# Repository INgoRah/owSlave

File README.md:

# owSlave2
Fork from https://git.smho.de/gw/?p=owSlave2.git;a=summary, License

I2C master code from an unofficial github repository for Peter Fleury's I2C library
http://homepage.hispeed.ch/peterfleury/avr-software.html#libs now cloned to
https://github.com/alx741/avr_i2c.git
License GPL v3

## Changes
Version 1.9, 2025-12-18
- Decreased button press min times
- DS1820: no periodic measurement by the watchdog timer any more. The
  temperature is measured on the master's Convert T (and once after
  start), like a real DS18x20; the master polls, e.g. once a minute.
  The watchdog is a watchdog again for these builds as well
  (WDT_ENABLED), the ADC averaging takes its 4 samples at once.
- DS1820 (dual ROM): Skip ROM + Convert T (CC 44) starts the
  measurement of all sensors on the bus at once. Other commands after
  Skip ROM are ignored.
- Buttons: the release after a long press is reported with at least
  11 (352 ms) as press time. The device sleeps once the long press is
  signaled and millis() stands still, the master (> 350 ms) took the
  release for a short press. A short press never reports 0 (that is
  the long press started), the press time is capped at 0xfe.
- Bootloader on long lines, as the application does it: a 0 sent is
  pulled low within a few cycles of the master's fall (was 2..3 us,
  against the master's active pullup) and held 50 us (OWT_WRITE, was
  30 us). With several devices on a long line the bits sent got lost
  (the INFO answer garbled, "no bootloader answers" in in10dfs).
- Bootloader: works with the slots of the DS2482 on a loaded line. In
  a write 0 slot the DS2482 keeps the line low for 64 us and starts
  the next slot 5.25 us later; the bootloader waited for the line to
  be high for 2..3 us first (against ringing), with the rise time of a
  long line that was missed and the next slot with it - all bits
  shifted, no answer (INFO all ff) or a wrong CRC. The falling edge is
  now taken from the edge flag of INT0 (polled, no interrupt), as the
  application does by its interrupt: seen however short the high was.
  Against ringing a fall starts a slot only if the line is low again
  2..4 us later, falls up to 25 us after it are part of the same slot.
- Bootloader: a 0 sent is held 40 us (was 50): with the RC oscillator
  10 % slow the work between two bytes did not fit before the next
  slot. The CRC16 is updated a bit at a time in its slot.
- Bootloader: the result of a page write is sent from the start of a
  byte of the master (page 0 of the ATtinys takes 18 ms, the master is
  reading by then), the presence pulse of another device lasting
  longer than its own is not taken for the next reset.
- ATmega: INT0 is set to low level before power down (ISC01 is in EICRA,
  not MCUCR as on the ATtinys): with the falling edge the device did not
  wake up from power down by the bus.
- Fix a bug, when the watchdog fires after any left over 1-wire activity (which is
  still in spec).
  This is solved with that soft watchdog timer of 1 second.
  That could have caused issues on broken masters when a transfer
  is stopped after reset and could have also blocked pin detection
- Watchdog behaviour changed: first a soft watchdog fires after 1s and
  resets internal states, alarms and triggers a hard watchdog
  for 60 ms if the system does not go to normal.
- status field retuns 0x08 for soft watchdog, 0x88 for hard (as before)
- Fix CRC overwrite when the config command is used. That was causing a
  fallback to fixed owids (compile time)

Version 1.8, 2024-11-28
- Dual DS2450 (ADC) support and minor fixes
- the cfg read on the custom space seems not to be working yet
  on dual ROM
- Alarm on watchdog reset

Version 1.7, 2024-11-22
- Timer based switch (supports one timer only)
- Single Pin configuration message and new custom config space (first byte = 1)
- Read out custom space by first writing one config byte with 1 then reading
- Auto toggle now signals the latch and the output

Version 1.5, 2021-11-28
- Temperature and Humidity support with DHT22 on pin PB0 (compile option)
  Humiditiy is reported in the byte #5 instead of FF

Version 1.4, 2021-10-27
- support BMP280 with dual rom with DS1820 on a soft I2C master
- report any latch change even for auto switch
- remove latch output on configured input pins

Version 1.3, 2021-01-14
- Split the files for 2408 and 1820
- In case of temperature support, regularly wake up and check alarms thresholds.
  This is using watchdog timer - power optimized.
- Temperature controlled switch (heating control, thresholds configurable
- Temperature change reporting (configurable)
- Read initial state for input switches of types CFG_PASS* and perform auto switch.
    Otherwise a thermostat might be ignored on restart and no heating active where
    it should
- per port pin intialization to reduce power if not connected (pull up not needed)

Version 1.2
- For PWM output (on ATTiny85 PB4 / PIO0 and ATTiny84 PA5) the all output latch bits
  are used for the duty cycle (bightnes), 0 for off
- PWM output level to be applied on change request (not only on switching it on)
- optimize touch sensor handling (active high, no bouncing, just rising edge with validation).
    POL and SW_ID to be implemented

Version 1.1
- Interrupt generation using the ow line low for 900 us
- Timer functions like in Arduino but on polling base within the loop. No wakeup from sleep
- Pin and push button validation
- Watchdog support:
    After 8 secs of invalid state a reset occurs (e.g. a hang in button validation).
    This also applies to pressing a button for 8 secs (force reset)
- Initial OneWire ID is initialized and copyied over to the end of EEPROM on
  first boot for reading next time.
- store new config / custom command or newid command feature

## To Do
[x] Generate alarm for latch even when auto switching
[x] Support for timer switches using upper auto switching bits [4..7]: 1 - 30 secs, 2 - 1 min, 3 - 2 mins .. 15 - 14 min.
[ ] Watchdog fires if switching PIO without polling/resetting alarm
[ ] regression testing signal generation and improvements (bus detection and delay)
[ ] Disarm interrupt on reset pulse and arm again afterwards.
    Needs check wether slave can cope with just a reset without ROM commands.
    Timeout after reset?
[ ] iButton type 2 interrupt (assert reset for long time).
    Needs master improvements detecting it and slave ASM code extending the reset low time
[ ] Dual 2408 with on PCF8473
[ ] Pin overlay for in and out using all 10 pins (reset and 1-wire not available)

## Issues
[ ] long press no longer working with outstanding changes
[ ] config save does not work sometimes
[ ] once setting PIO overides heating override ... fixed by pin change corrections?
[ ] If bad signals on the bus or power outage OW ID could be damaged. Needs protection

  # Documentation

  ## Configuration

  ### EEPROM Layout
  See eeprom.py script

  ### Configuration Definition
  CFG [0] config control, see below; reads 0xff
  CFG [1] default 0xff unused
  CFG [2] default 0xff unused
  SWx  [3..10]
    Auto switch an ouput on (short) press of this pin. Output starts with 1 (1 switches PIO0...).
    Example: SW4 = 0x01 switches PI0 on latch 4
    0x80 disables it,
    0x20 timer based switching, look up in custom config space
    0x40 reserved for long press auto switching, look up in custom config space
  CFGx [11..18] see CFG_xxx defines
  FEA [19] - Feature if bit is cleared: 
    0x1 can do temperature
    0x2 can do ADC for brightness read
    0x4 supports pin timers and extended auto switching
  Reserved [20]
  Version [21..22]
  Type [23]

  ### Config control
  Byte 0 of a config write (0x86) tells what the write is (CC_xxx in
  DS2408.h):

  Byte 0 | Write | Done after
  -------- | -------- | --------
  0x00, 0xff, 0x10 .. 0xff not below | config_info, saved with Version = 0x55 | 23 bytes
  0x01 | custom config (cfg_custom1, TIMER_SUPPORT), saved with byte 22 = 0x55 | 23 bytes
  0x02 | config_info2 (dual ROM), by its own write command for now | 23 bytes
  0x03 .. 0x0f | reserved, ignored | -
  0xB0 | bootloader: `B0 07 F8` (BL_ENTER_KEY and its complement) | 3 bytes
  0xDE | test: `DE AD op`, op 0x01 soft reset, 0x02 soft then hard reset, 0xff hard reset | 3 bytes

  The commands (0xB0, 0xDE) do not touch config_info, the bytes after
  the third are ignored. A config read starts with 0xff, written back
  as it is it is a plain config write.

## 1-Wire bootloader (ATmega88, ATmega168, ATtiny84, ATtiny85)

`bootloader/` is a bootloader for a firmware update over the 1-Wire bus
(in10dfs: write the image to `<rom>/firmware`), protocol in
`include/owbootloader.h`. It answers with the device's own ROM (from
the EEPROM). After a reset it starts the application at once, unless
the application asked for the update (config write `0xB0 0x07 0xF8`,
see "Config control", it jumps to the bootloader with BL_MAGIC in r24:r25) or there is
no valid application. Without anything to do for a minute it starts
the application again. An update broken off leaves no application:
the device stays in its bootloader, the update can be done again.

| | bootloader | application | fuses |
|---|---|---|---|
| ATmega88 | boot section, 2 KB at 0x1800 | 6144 bytes | efuse 0xF8: BOOTSZ 1024 words, BOOTRST |
| ATmega168 | boot section, 2 KB at 0x3800 | 14336 bytes | efuse 0xF8: BOOTSZ 1024 words, BOOTRST |
| ATtiny84/85 | 1600 bytes at 0x19C0 | 6592 bytes | efuse 0xFE: SELFPRGEN |

The ATtinys have no boot section: reset always starts at 0. Writing
page 0 the bootloader puts its own reset vector there and keeps the
application's on the last page of the flash, to start it by; a read
of page 0 gives the page as written. On the ATtiny85, without a 16 bit
timer, Timer0 is extended to 16 bit in software.

The environments: `atmega88`, `atmega168`, `attiny84-bl`, `attiny85-bl` for the
application (`-DBL_SUPPORT`), `<mcu>-boot` for the bootloader. By ISP,
once, the fuses and both together - an ISP upload erases the chip, the
upload of `<mcu>-boot` writes the application as well:

```sh
pio run -e attiny84-bl && pio run -e attiny84-boot -t fuses -t upload
```

`-t fuses` erases the chip, so only with the upload. Afterwards the
application is updated over the bus.

`test/bootloader/run.sh [mcu ...]` runs bootloader and application in
simavr against a 1-Wire master with the timing of a DS2482: into the
bootloader (on the ATtinys made by the test, simavr does not run the
application's 1-Wire there), INFO, Read and Search ROM, page writes, an
update as in10dfs does it, a reset in the middle of it, back to the new
application and in once more. It needs the simavr headers (libsimavr-dev,
or SIMAVR_INC).

## Custom timer command

0xC5 | FEAT/PIN | TYPE | VAL1 | VAL2
read back 16 bit CRC over command and all bytes
TYPE: see TMR_TYPE_xxx definitions
VAL1: Time in 10ms or config for non static switch. If 0 use the confiugred default time.
      In case of type E3 (TMR_TYPE_BRIGHTNESS) or E5 (TMR_TYPE_THRESHOLD) 
      brightness or lower threshold value for darkness switching.
      Brightness is the inversed ligth - means 0xff dark and 0 for very bright.
      code: switch only if brightness >= cfg_custom1[1]
      Configuring threshold will also store the entire custom cfg in EEPROM
VAL2: Level 0 .. 255 for PWM output

Status represents a running timer with 0x20 or a dimming down with 0x40

# 1-wire implementation (from tm3e.de / German)

## Files

Datei  | Beschreibung |
-------- | -------- |
OWPinInterrupt.s | Interrupt für Pegeländerungen am 1-Wire Pin
OWTimerInterrupt.s | Timer Interrupt für Zeitmessungen
OWConfig.s | Allgemeine Konfiguration (Register und Speicher Belegung, Auswahl der Konfiguration für den speziellen AVR, Macros)
OWSet_ATTINYX4.s | Spezielle Konfiguration für ATTINY24 - ATTINY84
OWSet_ATTINYX5.s | Spezielle Konfiguration für ATTINY25 - ATTINY85
OWCRC8.s | CRC8 Berechnung (Wird je nach Gerät ausgewählt)
OWCRC16.s | CRC16 Berechnung (Wird je nach Gerät ausgewählt)
OWRomFunctions.s | Alle ROM-Funktionen, sowie die Funktionalität zur Änderung der OW-Pin
Diese Dateien stehen im Unterverzeichnis "common". Für jedes 1-Wire Gerät wird ein weiteres Unterverzeichnis angelegt und dort ist mindestens jeweils eine .c Datei mit dem Hauptprogramm und eine .s Datei mit den spezifischen Assemblerroutinen für das Gerät.

## Register und Variablen
Alle Registerbezeichnungen beginnen mit "r_", so dass sie nicht mit Variablen verwechselt werden können. Wenn es dazugehörige Variablen im SRAM gibt, dann stehen sie gleich dahinter.

 Bezeichnung | Nr. | Hauptfunktion |
 -------- | -------- | --- |
 r_temp | 16 | temporäre Zwischenspeicherung
 r_rwbyte / rwbyte | 17 | aktuelles Byte welches gelesen oder geschrieben wird
 r_temp2 | 18 | temporäres Zusatzregister, wenn eins nicht ausreicht
 r_bcount / bcount | 19 | Bit, welches gerade behandelt wird ist 1, Bit wird druchgeschoben. r_bcount=0 bedeutet: nächstes Byte muss behandelt werden
 r_mode / mode | 20 | Aktueller Zustand/Funktion, OW_SLEEP->Lehrlauf, Definition der ROM Commands in OWRomFunctions.s, gerätespezifische Konstanten in der .s Datei im Geräteverzeichnis. Nach dem Wert in mode werden über die Sprungtabelle (handle_stable) die entsprechenden Routinen ausgewählt.
 r_sendflag / sendflag | 21 |  0 => Slave empfängt Daten vom Master, 1=> Slave sendet Daten zum Master
 r_bytep / bytep | 22 | Pointer auf das nächste (od. aktuelle) Byte
 r_crc | 23 | Hilfsvariable für die CRC-Berechnung
 srbyte |   | Aktuelles Byte für SEARCH_ROM
 alarmflag |   | Für das Suchen von Geräten im Alarmmodus (z.B. beim DS18B20)
 owid |   | Speicher für die 1-Wire-ID
 zl / zh | 30/31 | Speicherzugriff
 reset_indicator |   | Zeigt Hauptprogramm, dass ein Resetimpuls empfangen wurde
 gcontrol |   | Kommunikation mit dem Programmteilen die nicht in der Interruptroutine laufen
Einige Register werden in der SEARCH_ROM-Routine anders verwendet, um zusätzliche Push und Pop Befehle einzusparen.

Die vom Timing aus betrachtet kritischste Sitation ist wenn der Slave eine "0" an den Master sendet. Der Master zieht die Leitung auf Low und der Slave muss möglist in 6 µs die Leitung auch auf Low ziehen. Der DS9490 lässt die Leitung unter Umständen noch schneller wieder auf High (5V) springen. Nach der 1-Wire Spezifikation muss der Slave die Leitung nach 15 µs auf Low sein, denn dann liest der Master aus. Das ist kein Problem für den AVR. Es ist aber mein Ziel, dass zwischen dem Master-Low und dem Slave-Low keine Pause ist (die Leitung nicht auf High springt).
Es muss also in der Interruptroutine schnell entschieden werden ob eine "0" gesendet werden muss. Eine normal Variable in einem SRAM-Bereich müsste dazu erst in ein Register geladen werden. Das Register müsste vorher gesichert werden. Ein schnellerer Weg ist es, wenn ein ungenutztes Bit in einem I/O-Register des AVR für die Entscheidnugn genutzt wird.

Aus diesem Grund wurde das DDR Bit des Reset Pins für diese Entscheidung zweckentfremdet. Die Reset Leitung wird normalerweise nur zum Programmieren genutzt und da stört diese Anwendung nicht. Um das Reset-Pin als vollwertiges I/O-Pin zu nutzen muss erst eine FUSE gesetzt werden. Dann geht das Programmieren aber nur noch über die Hochvoltprogrammierung.

Es gibt also noch eine weiter Variable (ZEROMAKER), die nicht direkt im Quelltext auftaucht.

Folgende Abbildungen verdeutlicht diesen Zusammenhang nocheinmal:

Variable im SRAM  -> 9,3 µs bis Bus Low
Variable im SRAM -> 9,3 µs bis Bus Low

Variable im I/O Register -> Leitung nicht zwischendurch auf High
Variable im I/O Register -> Leitung nicht zwischendurch auf High

Die beiden Verläufe sind von einem Test mit einem MOSFET (2N7000) als Pegelwandler von 5V am 1-Wirebus und 3V am ATTINY84.

## Programmablauf
Herzstück der Simulation ist die Interruptroutine die bei einer fallenden Flanke am 1-Wire Bus aufgerufen wird. In der neuen Software gibt es hier keinen unterschied zwischen den verschiedenen Zuständen wie Reset, Searchrom usw. Bei einem Reset wird ersteinmal ganz normal ein Bit gelesen. Da keine weitere fallende Flanke kommt, wird irgend wann der Timer Interrupt aufgrufen und Prüft ob die Leitung noch Low ist. Der Timer-Interrupt gibt dann entsprechend den Presents Impuls aus und schaltet auf OWM_READ_COMMAND.

Die Eigentlichen Funktionen werden bei handle_byte ausgeführt. Dort Springt das Programm anhand von einer Sprungtabelle und dem Wert in mode sehr effizient an die Stelle, wo der aktuelle Zustand bearbeitet wird.

Bei dem Searchrom-Algorithmus, wo jeweils zwei Bits gesendet (vom Slave gesndet) werden und ein Bit empfangen wird, bekommt der Bitzähler bcount nur entsprechend kleinere Werte und die handle_byte Funktion wird öfterer aufgerufen.

Beim Senden erfolgen die Berechnungen für das nächste Byte zwischen der fallenden Flanke vom Master bis zu der Zeit, in dem der Slave die Leitung wieder frei gibt, wenn denn eine 0 gesendet wird. Beim Empfangen erfolgen die Berechnungen nachdem die Leitung ausgelesen wurde bis maximal zum nächsten Low-Impuls vom Master (etwas eher sollte es schon sein).

Wichtig ist, dass nach einem handle_byte beim Empfangen das sendflag kontroliert wird. Wenn das nächste Byte gesendet wird muss der ZEROMARKER entsprechend gesetzt werden.

Im bei einem Timer Interupt wird geprüft, ob die Leitung Lange genug Low ist, damit der Impuls als Reset Impuls erkannt wird. Dazu gibt es noch die zweite Zeit OWT_RESET2. Die Zeiten wie auch OWT_READ und OWT_WRITE durch Polling eingehalten. Der Timer-Interrupt wird nur bei einem "Timeout" nach einer Fallenden Flanke ausgelöst.

### Übersicht über die Zustände bei handle_byte
 In der Datei OWRomFunctions.s sind die grundlegenden Zustände für die 1-Wire Simulation definiert. Diese sind bei jedem Gerät gleich. Deshalb gibt es hier eine kurze Beschreibung dazu:

|Zustand (mode)|Beschreibung
| --- | ---
OW_SLEEP | Warten auf einen Resetimpuls. Alle fallenden Flanken auf dem Bus müssen dazu überprüft werden
OW_READ_ROM_COMMAND | Nach erfolgreichen Reset wird ein Befehl zur Zugriffskontrolle gelesen.
OW_MATCHROM | Empfangen einer ID und prüfen ob es die Eigene ist
OW_SEARCHROMS | Search-Rom-Algorithmus: Senden eines Bits aus der ID und danach die Negation (Complement) des Bits
OW_SEARCHROMR | Search-Rom-Algorithmus: Empfangen des Steuerbits vom Master
OW_READROM | Wenn nur ein 1-Wire Gerät am Bus ist kann die ID ausgelesen werden.
OW_WRITE_NEWID1 | Schreiben einer neuen ID in den ID-Zwischenspeicher
OW_READ_NEWID1 | Kontrolieren der ID aus den Zwischenspeicher
OW_SET_NEWID1 | Übernehmen der ID aus den Zwischenspeicher in den ID-Speicher (EEPROM)
OW_FIRST_COMMAND | Kein Zustand, enthällt die Nummer des nächsten Zustandes für die gerätespezifischen Zustände (Befehle)
1 Nur wenn die Möglichkeit zur ID-Veränderung eingeschaltet ist 

Die Zustände ensprechen nicht unbedingt immer den 1-Wire Command-Codes die behandelt werden. Diese sind deshalb nocheinmal in der folgenden Tabelle angegeben:

Code | Beschreibung
 --- | ---
0x55 | MATCH ROM: selektieren eines Gerätes anhand einer ID
0xF0 | SEARCH ROM: Suchalgorithmus für die angeschlossenen Geräte
0xCC | SKIP ROM: Überspringen von MATCH ROM wenn nur ein Gerät am Bus
0x33 | READ ROM: Lesen der ID wenn nur ein Gerät am Bus
0xEC | ALARM SEARCH: SEARCH ROM für Geräte bei denen das Alarm-Flag gesetzt ist
0x75 | WRITE NEWID: Schreiben einer neuen ID in den Zwischenspeicher
0xA7 | READ NEWID: Lesen der ID aus dem Zwischenspeicher
0x79 | SET NEWID: Übernehmen der neuen ID
Nach OW_READ_ROM_COMMAND bzw. nach OW_READ_COMMAND werden die Codes gebrüft. Dafür gibt es in der Datei OWRomFunctions.s zwei Makros. Wenn das Sprungziel im bereich von -63 und +64 Befehlen liegt kann das Makro cjmp verwendet werden. Alternativ, wenn der Linker fehler bringt, muss das aufwändigere Makro cljmp verwendt werden. Dabei wird mehr Speicher benötigt und die Ausführung dauert länger.

In der Regel wird zunächst zu einer Initialisierungsroutinge (hrc_set_[befehl]) gesprungen, die den neuen Zustand und alle anderen Parameter einstellt. In der Sprungtabelle (handle_stable) steht der Sprungbefehl zu der Routine, die den aktuellen Zustand behandlet (rjmp h_[Zustand]).

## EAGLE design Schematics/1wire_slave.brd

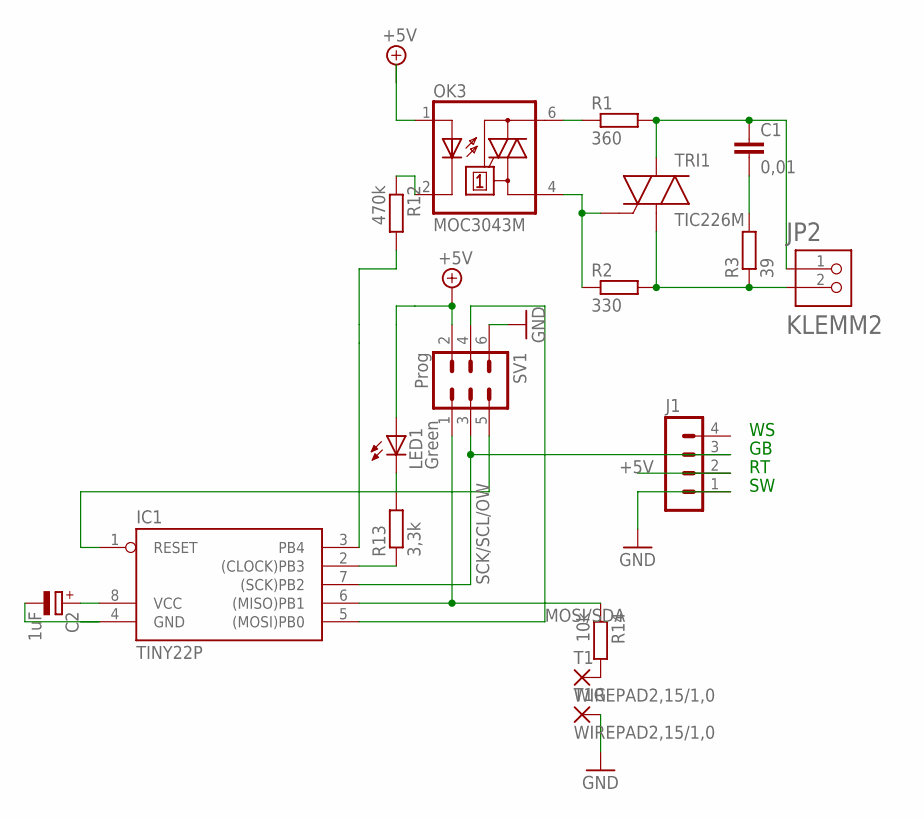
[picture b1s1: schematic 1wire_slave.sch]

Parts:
C1: 0,01; C15B6
C2: 1uF; E2,5-6E
IC1: TINY22P; DIL08
J1: MA04-1
JP2: KLEMM2
LED1: Green; LED3MM
OK3: MOC3043M; DIL06
R1: 360; 0204/7
R2: 330; 0204/7
R3: 39; 0207/15
R12: 470k; 0207/12
R13: 3,3k; 0207/10
R14: 10k; 0204V
SV1: Prog; MA03-2
T1, T1G: WIREPAD2,15/1,0; 2,15/1,0
TRI1: TIC226M; TO-220A

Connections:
+5V: C2.+, IC1.8 (VCC), J1.2, LED1.A, OK3.1 (A), SV1.2
GND: C2.-, IC1.4 (GND), J1.1, SV1.6, T1G.1
MOSI/SDA: IC1.5 ((MOSI)PB0), SV1.4
unnamed: JP2.2, R2.2, R3.1, TRI1.1 (A1)
unnamed: C1.1, JP2.1, R1.2, TRI1.2 (A2)
unnamed: IC1.3 (PB4), R12.2
unnamed: R14.2, T1.1
unnamed: OK3.4 (A1), R2.1, TRI1.3 (G)
unnamed: C1.2, R3.2
unnamed: OK3.6 (A2), R1.1
unnamed: OK3.2 (C), R12.1
unnamed: IC1.2 ((CLOCK)PB3), R13.1
unnamed: LED1.K (C), R13.2
RESET: IC1.1 (RESET), SV1.5
SCK/SCL/OW: IC1.7 ((SCK)PB2), J1.3, SV1.3
SHWO: IC1.6 ((MISO)PB1), R14.1, SV1.1

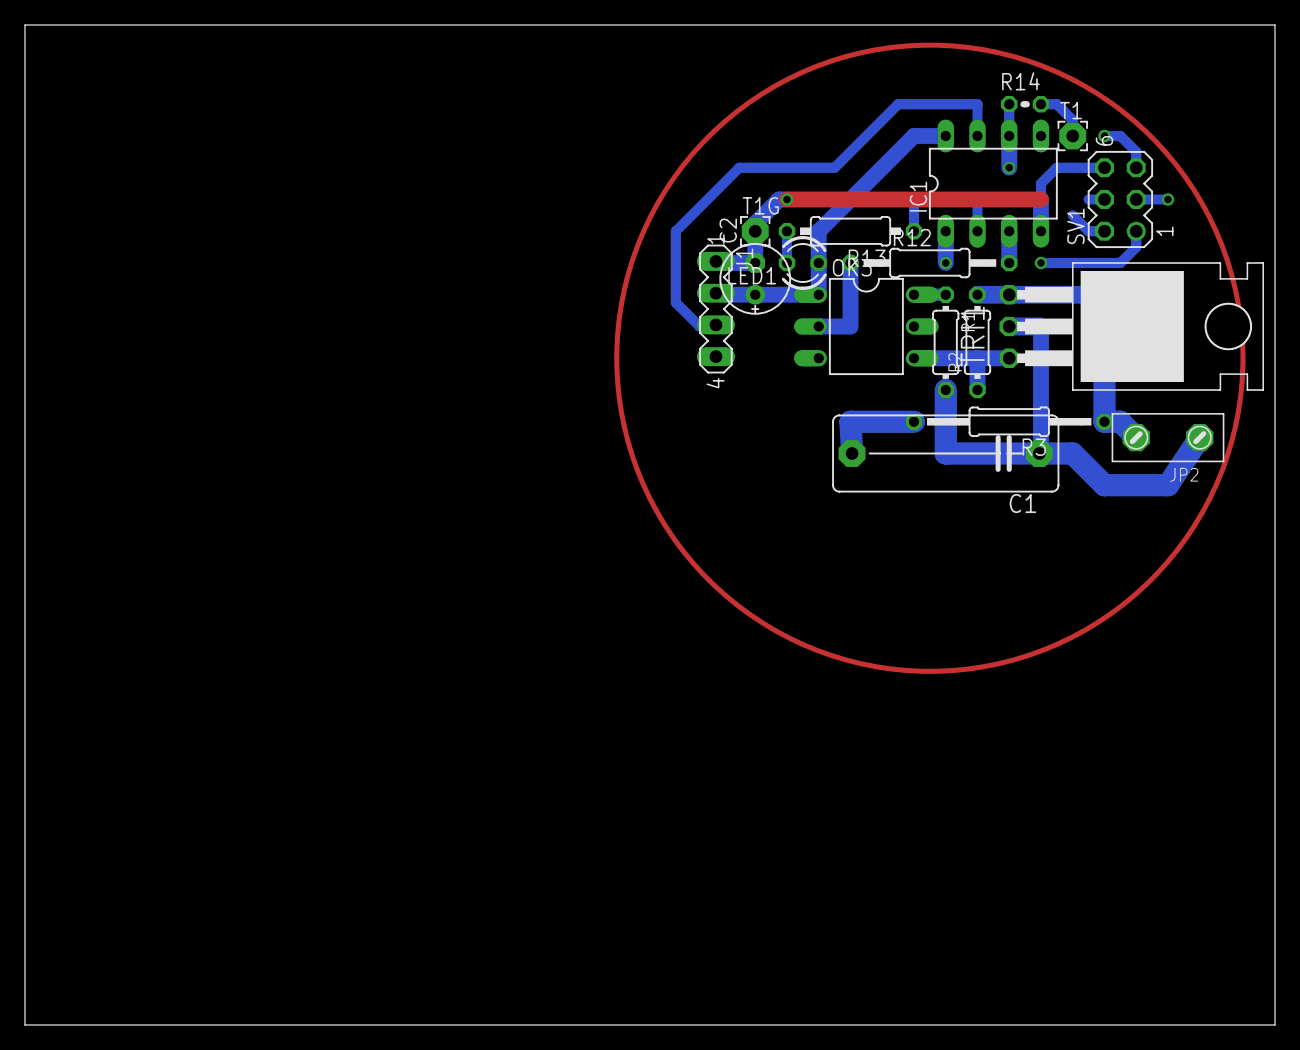
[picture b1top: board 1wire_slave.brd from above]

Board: 2 copper layers, 100.0 x 80.0 mm, 17 parts (0 on the bottom side), 16 nets.

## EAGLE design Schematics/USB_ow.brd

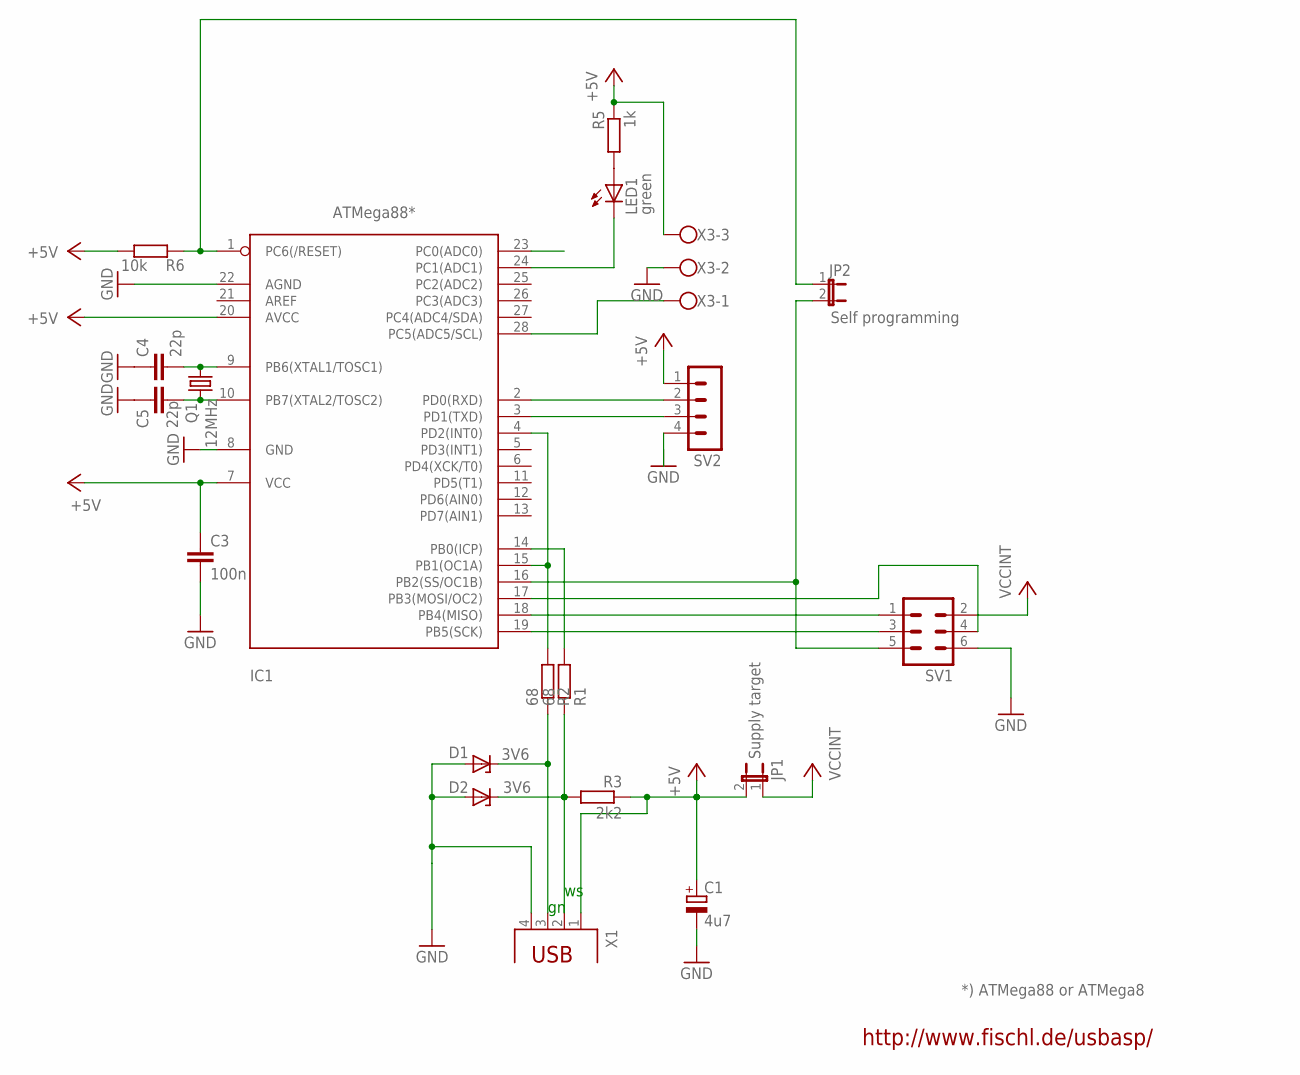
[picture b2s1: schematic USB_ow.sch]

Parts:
C1: 4u7; E2,5-5
C3: 100n; C025-024X044
C4, C5: 22p; C025-024X044
D1, D2: 3V6; DO34Z7
IC1: ATMega88*; DIL28-3
JP1: Supply target; JP1
JP2: Self programming; JP1
LED1: green; LED3MM
Q1: 12MHz; HC49/S
R1, R2: 68; 0207/10
R3: 2k2; 0207/10
R5: 1k; 0207/10
R6: 10k; 0207/10
SV1: MA03-2
SV2: MA04-1
X1: PN61729
X3: W237-103

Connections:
+5V: C1.+, C3.1, IC1.7 (VCC), IC1.20 (AVCC), JP1.2, R3.1, R5.1, R6.1, SV2.1, X1.1, X3.3
D+: D1.C, R2.1, X1.3
D-: D2.C, R1.1, R3.2, X1.2
GND: C1.-, C3.2, C4.1, C5.1, D1.A, D2.A, IC1.8 (GND), IC1.22 (AGND), SV1.6, SV2.4, X1.4, X3.2
unnamed: IC1.16 (PB2(SS/OC1B)), JP2.2, SV1.5
unnamed: IC1.17 (PB3(MOSI/OC2)), SV1.4
unnamed: IC1.19 (PB5(SCK)), SV1.3
unnamed: IC1.18 (PB4(MISO)), SV1.1
unnamed: IC1.4 (PD2(INT0)), IC1.15 (PB1(OC1A)), R2.2
unnamed: IC1.28 (PC5(ADC5/SCL)), X3.1
unnamed: IC1.24 (PC1(ADC1)), LED1.K (C)
unnamed: IC1.14 (PB0(ICP)), R1.2
unnamed: C4.2, IC1.9 (PB6(XTAL1/TOSC1)), Q1.2
unnamed: C5.2, IC1.10 (PB7(XTAL2/TOSC2)), Q1.1
unnamed: LED1.A, R5.2
RESET: IC1.1 (PC6(/RESET)), JP2.1, R6.2
RXD: IC1.2 (PD0(RXD)), SV2.2
TXD: IC1.3 (PD1(TXD)), SV2.3
VCCINT: JP1.1, SV1.2

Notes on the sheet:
http://www.fischl.de/usbasp/
*) ATMega88 or ATMega8

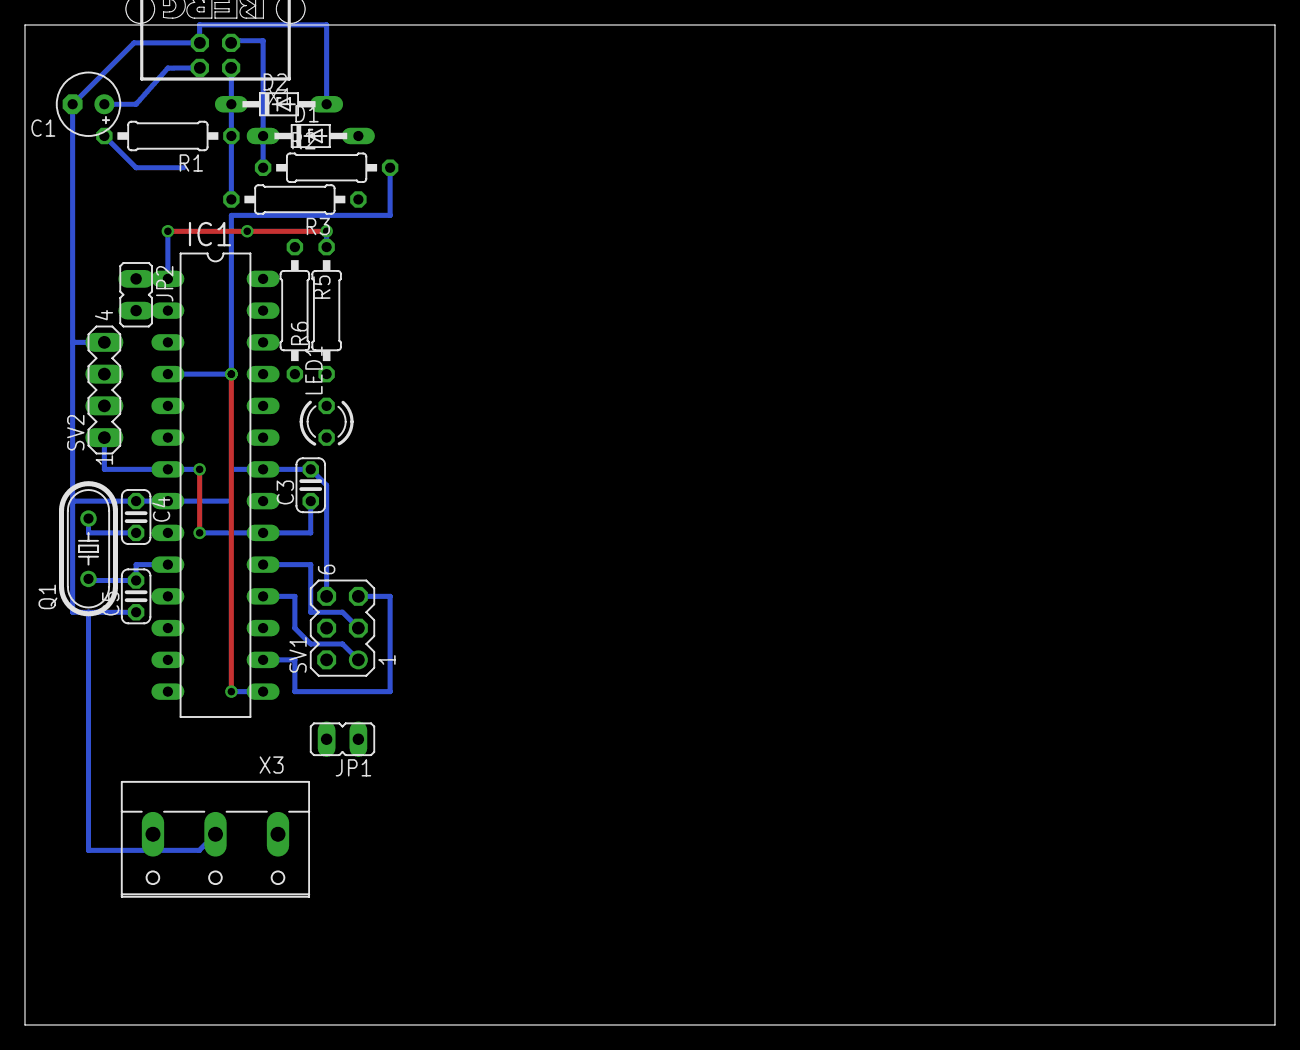
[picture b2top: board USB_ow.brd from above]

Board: 2 copper layers, 100.0 x 80.0 mm, 20 parts (0 on the bottom side), 19 nets.

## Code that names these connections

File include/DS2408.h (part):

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#endif
#define PIN_DDR DDRB

#define PIN_PIO0 _BV(PB1)
#define PIN_PIO1 _BV(PB0)
#define PIN_PIO2 _BV(PB2)
#define PIN_PIO3 _BV(PB3)
#define PIN_PIO4 _BV(PB4)
#define PIN_PIO5 _BV(PB5)
#define PIN_PIO6 _BV(PB6)
#define PIN_PIO7 _BV(PB7)

#define LED2 _BV(PC3)
#define LED _BV(PC1)

#ifdef WITH_LEDS
#define	LED_ON() do { DDRC |= LED;PORTC &= ~LED; }while(0)
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#define PIN_REG PINB
#define PIN_DDR DDRB

#define PIN_PIO0 _BV(PB4) /* light : ouput/PWM */
#define PIN_PIO1 _BV(PB3)
#define PIN_PIO2 _BV(PB1)
#define PIN_PIO3 _BV(PB0) /* light switch: input */
#define LED _BV(PB3)
#ifdef WITH_LEDS
#define	LED_ON()  do { DDRB |= LED;  PORTB &= ~LED; } while(0)
#define	LED_OFF() do { DDRB &= ~LED; PORTB |= LED;  } while(0)
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#define PIN_PIO7 (1<<PINA7)
#ifdef WITH_LEDS
#define LED _BV(PA0)
#define LED2 _BV(PB0)

#define	LED_ON() do { DDRA |= LED;PORTA &= ~LED; }while(0)
#define	LED_OFF() do {DDRA &= ~LED;PORTA |= LED; }while(0)
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
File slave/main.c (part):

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}
#endif

/* PB1 */
#if defined(PCINT1_vect)
ISR(PCINT1_vect)
{
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#ifdef HAVE_UART
	serial_init();
#else
	DDRD |= _BV (PD0) | _BV (PD1);
<<<<<<< HEAD
#endif /* HAVE_UART */
#else
	DDRB |= _BV(PB3) | _BV(PB4);
#endif /* __AVR_ATmegax8__ */
=======
#endif
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
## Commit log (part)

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2020-06-19 Initial working IR sender
2020-06-19 Version Update with more decent commands and ATMEGA support
    - Introducing some more abstractions for ATMEGA and ATTINY reusing from Arduino
    - Introduce familiy compile switch
    - Abstraction interface for pinSetup
    - Reuse timer tick concept from Arduino (but use timer1)
    - Application command structure changed
    - Supporting input button with debouncing. Fires and interrupt on OW line after releasing the button
2020-06-19 Make code more generic for different applications
    Debugging support via uart
    Pin abstraction from Arduino
    Timer like Arduino but Timer1 used instead of Timer0
2020-06-19 Button handling improvements
2020-06-19 Family handling
2020-06-19 closing slave1
2020-07-09 first working button with T85 and ATMEGA168 with UART debugging
2020-07-09 temp change
2020-07-09 Initial with interrupt signaling (beta)
2020-07-09 button first validation success
2020-07-09 Button working with 1wire and power down
    OWID read from EEPROM
    two registers of pin configuration (buttons and output)
    Signal generation mask added
    data read not working - blocking buttons somehow. Stack?
2020-07-09 Adding test code and clean up
2020-07-09 add schematics
2020-07-09 Remote configuration
    Stabilization
    Add version in config_info
    No signal generation on PIO change, needs latch clear (not yet covered in unit tests)
2020-08-30 Header file split
2020-08-30 Prepare test and simulation env
2020-09-06 Code optimization
    Draft WDT, but running in endless restart once fired
    Test vectors and regression testing with simulation target
2020-09-12 Watchdog implemented and verified
    Test on AT85 successful
    Optimized init code copying over the OWID for the original code (at the end of the EEPROM)
2020-09-20 Temp
2020-11-11 PWM on T84 (tested) and T85
    Support for active high signals like touch or PIR
2020-11-13 Update for active high or low pins (no pull up, no validation)
    Add temperature sensor (output latch == 0x44)
    store configuration if version id sent is 0x55
2020-11-13 docu
2020-12-05 PWM support for T84 and T85
2020-12-05 Rework directory:
    - move subfolder OwSlave2 to top
    - remove old slave code
2020-12-31 Improve pin config by individually assigning the by config_info
2021-01-04 Dual ROM working with alarm only on the DS2408 Remove owid read from asm code (done in C different location)
2021-01-06 Add draft TFT display (ST7735S, green tab)
2021-01-06 Display fields (very custom)
2021-01-25 Dual ROM working with alarm on both owids (DS2408 and DS1820)
    Remove owid read from asm code (done in C different location)
    Timer based temperature update and improvements
    Temperature change reporting (alarm configurable)
    Auto switch based on temperature (configurable)
    Split the files for 2408 and 1820
    Pin configuration improvements
2021-10-27 Adding BMP280 support via soft I2C (flexible pin assignment) using PB0 and PB1
    Avoid setting output latch on inputs causing latch in inconsistent state
2021-10-27 Support UNIT test style testing (still using simulation)
2021-11-28 Add DHT22 handling
    Split the sensors into files for BMP280 and DHT22
    Report humidity on byte#5 instead of FF
2021-11-28 Add changelog
2022-06-18 Code optimization
2022-06-18 Fix wrong PIO state for OUT_HIGH
    Increase PWM stages to 63
2023-10-15 Minor update: increase validation time for temp
2023-10-26 Check CRC on owid from EEPROM and otherwise fall back
    to a predefined one.
    Python script to calc the CRC and program it
2023-10-27 Workaround for failing for loop (stack?)
2024-11-24 Extended timed pin
    Extended timer (only one) support with new timer command and custom config space mainly for auto switching
2024-11-25 Draft (but working) DS2450 (ADC) support
2024-11-27 Bugfix: Do not start a timer if pin is already switched on Add test cases
2024-12-04 DS2450 (ADC) support
2025-02-13 Add draft ci workflow
2025-11-16 eeprom prog
2025-12-17 insert sw watchdog
2025-12-27 Watchdog timer fixes
    - Fix a bug, when the watchdog fires after any left over 1-wire activity (which is
    still in spec).
    - Watchdog behaviour changed: first a soft watchdog fires after 1s and
    resets internal states, alarms and triggers a hard watchdog
    for 60 ms if the system does not go to normal.
    - status field retuns 0x08 for soft watchdog, 0x88 for hard (as before)

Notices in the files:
slave/main.c:
Copyright (C) 2012  Tobias Mueller mail (at) tobynet.de
Copyright (C) 2018  INgo.Rah@gmx.net
This program is free software: you can redistribute it and/or modify
it under the terms of the GNU General Public License as published by
the Free Software Foundation, either version 3 of the License, or
any later version.
